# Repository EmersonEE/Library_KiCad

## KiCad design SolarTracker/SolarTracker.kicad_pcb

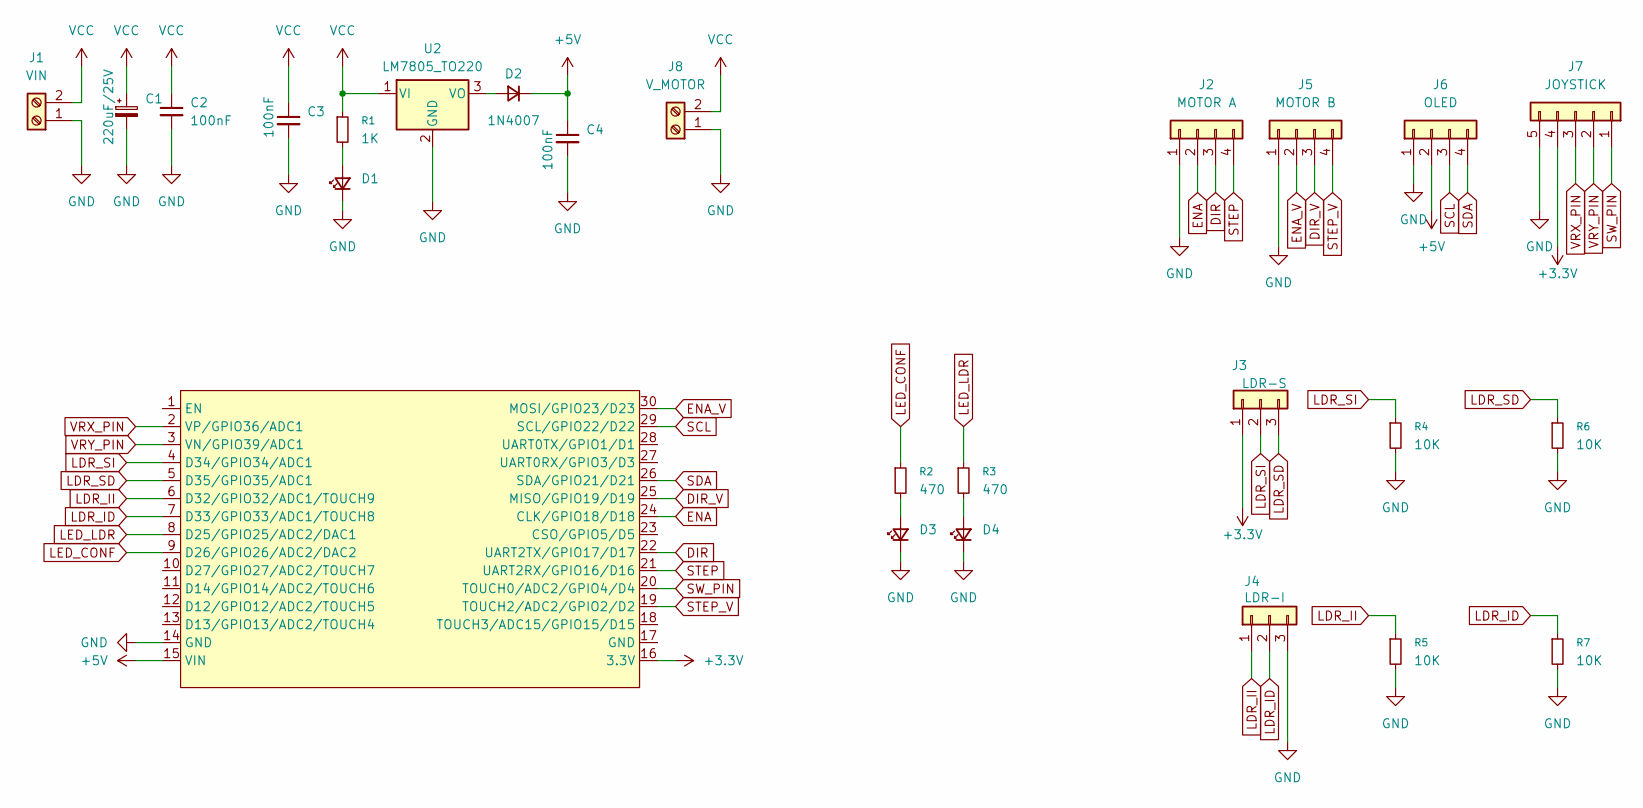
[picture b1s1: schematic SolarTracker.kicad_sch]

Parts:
C1: 220uF/25V; CP_Radial_D6.3mm_P2.50mm
C2, C3, C4: 100nF; C_Disc_D3.8mm_W2.6mm_P2.50mm
D1, D3, D4: LED_D5.0mm
D2: 1N4007; D_A-405_P10.16mm_Horizontal
J1: VIN; TerminalBlock_Phoenix_MKDS-1,5-2-5.08_1x02_P5.08mm_Horizont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
J2: MOTOR A; Molex_KK-254_AE-6410-04A_1x04_P2.54mm_Vertical
J3: LDR-S; Molex_KK-254_AE-6410-03A_1x03_P2.54mm_Vertical
J4: LDR-I; Molex_KK-254_AE-6410-03A_1x03_P2.54mm_Vertical
J5: MOTOR B; Molex_KK-254_AE-6410-04A_1x04_P2.54mm_Vertical
J6: OLED; PinSocket_1x04_P2.54mm_Vertical
J7: JOYSTICK; PinSocket_1x05_P2.54mm_Vertical
J8: V_MOTOR; TerminalBlock_Phoenix_MKDS-1,5-2-5.08_1x02_P5.08mm_Horizont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
R1: 1K; R_Axial_DIN0207_L6.3mm_D2.5mm_P10.16mm_Horizontal
R2, R3: 470; R_Axial_DIN0207_L6.3mm_D2.5mm_P10.16mm_Horizontal
R4, R5, R6, R7: 10K; R_Axial_DIN0207_L6.3mm_D2.5mm_P10.16mm_Horizontal
U1: ESP32_DevKit_V1_DOIT; ESP32_DEVKIT_V1_E32
U2: LM7805_TO220; TO-220-3_Vertical

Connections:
+3.3V: J3.1, J7.4, U1.16 (3.3V)
+5V: C4.1, D2.1 (K), J6.2, U1.15 (VIN)
DIR: J2.3, U1.22 (UART2TX/GPIO17/D17)
DIR_V: J5.3, U1.25 (MISO/GPIO19/D19)
ENA: J2.2, U1.24 (CLK/GPIO18/D18)
ENA_V: J5.2, U1.30 (MOSI/GPIO23/D23)
GND: C1.2, C2.2, C3.2, C4.2, D1.1 (K), D3.1 (K), D4.1 (K), J1.1, J2.1, J4.3, J5.1, J6.1, J7.5, J8.1, R4.2, R5.2, R6.2, R7.2, U1.14 (GND), U2.2 (GND)
LDR_ID: J4.2, R7.1, U1.7 (D33/GPIO33/ADC1/TOUCH8)
LDR_II: J4.1, R5.1, U1.6 (D32/GPIO32/ADC1/TOUCH9)
LDR_SD: J3.3, R6.1, U1.5 (D35/GPIO35/ADC1)
LDR_SI: J3.2, R4.1, U1.4 (D34/GPIO34/ADC1)
LED_CONF: R2.1, U1.9 (D26/GPIO26/ADC2/DAC2)
LED_LDR: R3.1, U1.8 (D25/GPIO25/ADC2/DAC1)
unnamed: D1.2 (A), R1.2
unnamed: D2.2 (A), U2.3 (VO)
unnamed: D3.2 (A), R2.2
unnamed: D4.2 (A), R3.2
SCL: J6.3, U1.29 (SCL/GPIO22/D22)
SDA: J6.4, U1.26 (SDA/GPIO21/D21)
STEP: J2.4, U1.21 (UART2RX/GPIO16/D16)
STEP_V: J5.4, U1.19 (TOUCH2/ADC2/GPIO2/D2)
SW_PIN: J7.1, U1.20 (TOUCH0/ADC2/GPIO4/D4)
VCC: C1.1, C2.1, C3.1, J1.2, J8.2, R1.1, U2.1 (VI)
VRX_PIN: J7.3, U1.2 (VP/GPIO36/ADC1)
VRY_PIN: J7.2, U1.3 (VN/GPIO39/ADC1)

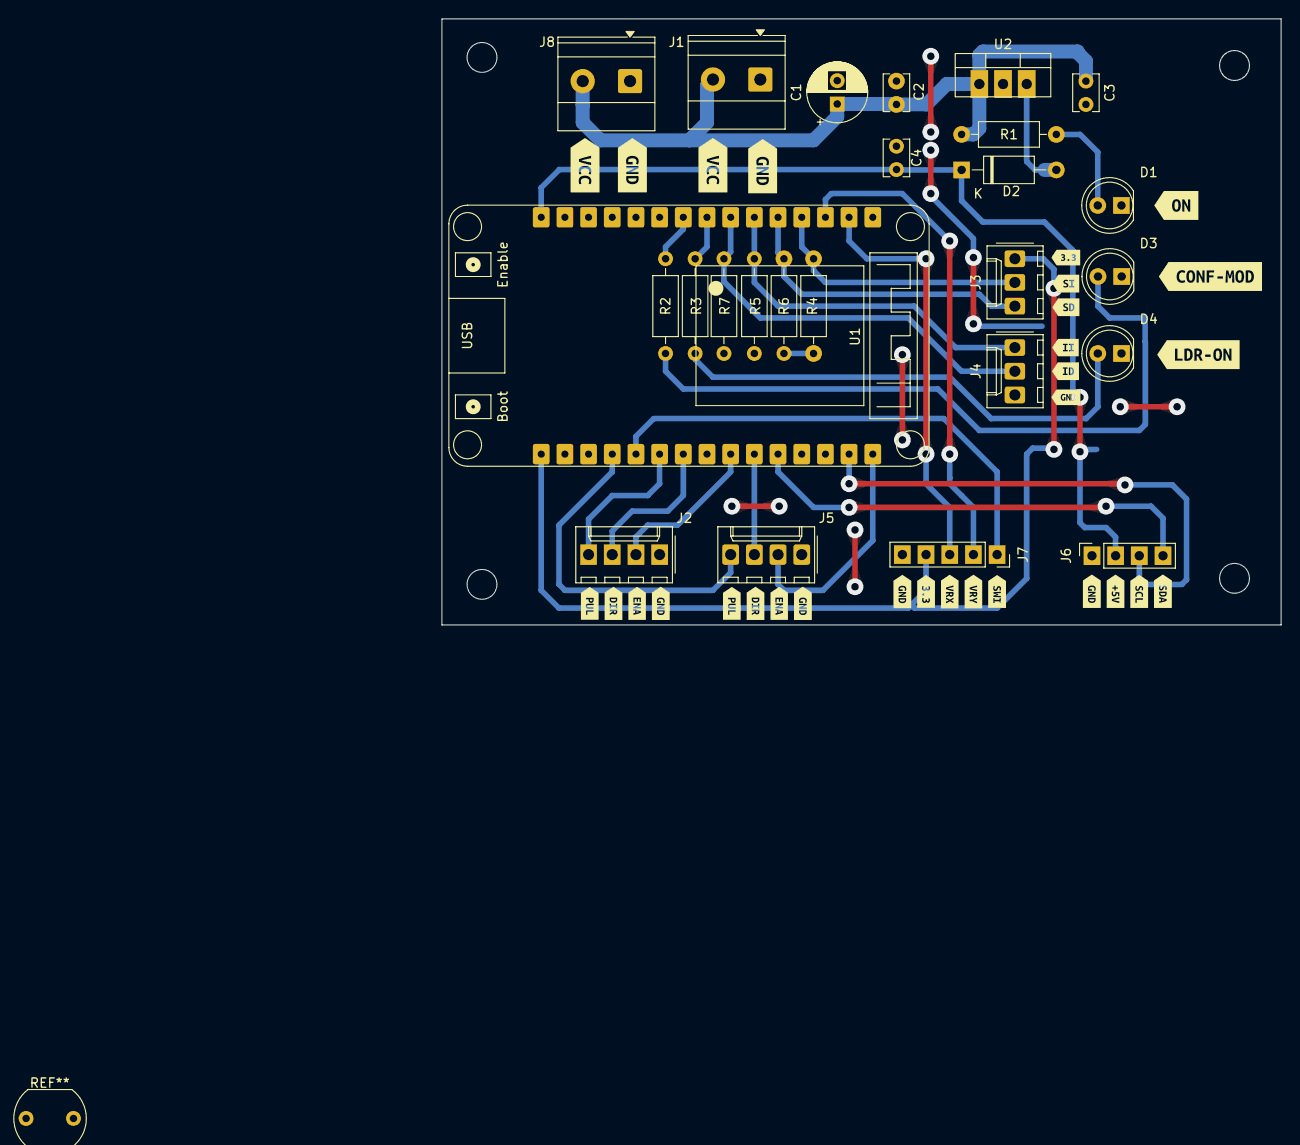
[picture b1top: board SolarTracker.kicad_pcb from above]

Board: 2 copper layers, 90.0 x 65.0 mm, 55 parts (0 on the bottom side), 25 nets.

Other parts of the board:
kibuzzard-67F1E4A8: G***; kibuzzard-67F1E4A8
kibuzzard-67F1E4B2: G***; kibuzzard-67F1E4B2
kibuzzard-67F1E4DB: G***; kibuzzard-67F1E4DB
kibuzzard-67F1E4E2: G***; kibuzzard-67F1E4E2
kibuzzard-67F1E4EA: G***; kibuzzard-67F1E4EA
kibuzzard-67F1E5DB, kibuzzard-67F1E5DB#2: G***; kibuzzard-67F1E5DB
kibuzzard-67F1E5E3, kibuzzard-67F1E5E3#2: G***; kibuzzard-67F1E5E3
kibuzzard-67F1E5F0, kibuzzard-67F1E5F0#2, kibuzzard-67F1E5F0#3: G***; kibuzzard-67F1E5F0
kibuzzard-67F1E6A7: G***; kibuzzard-67F1E6A7
kibuzzard-67F1E6AC: G***; kibuzzard-67F1E6AC
kibuzzard-67F1E47E: G***; kibuzzard-67F1E47E
kibuzzard-67F1E62A: G***; kibuzzard-67F1E62A
kibuzzard-67F1E66D: G***; kibuzzard-67F1E66D
kibuzzard-67F1E67F: G***; kibuzzard-67F1E67F
kibuzzard-67F1E69E: G***; kibuzzard-67F1E69E
kibuzzard-67F1E623: G***; kibuzzard-67F1E623
kibuzzard-67F1E673: G***; kibuzzard-67F1E673
kibuzzard-67F1E679: G***; kibuzzard-67F1E679
kibuzzard-67F1E689: G***; kibuzzard-67F1E689
kibuzzard-67F1ECE8: G***; kibuzzard-67F1ECE8
kibuzzard-67F1ECF6: G***; kibuzzard-67F1ECF6
kibuzzard-67F1ECFC: G***; kibuzzard-67F1ECFC
kibuzzard-67F1ED00: G***; kibuzzard-67F1ED00
kibuzzard-67F1ED0E: G***; kibuzzard-67F1ED0E
kibuzzard-67F1ED07: G***; kibuzzard-67F1ED07
kibuzzard-67F1ED13: G***; kibuzzard-67F1ED13

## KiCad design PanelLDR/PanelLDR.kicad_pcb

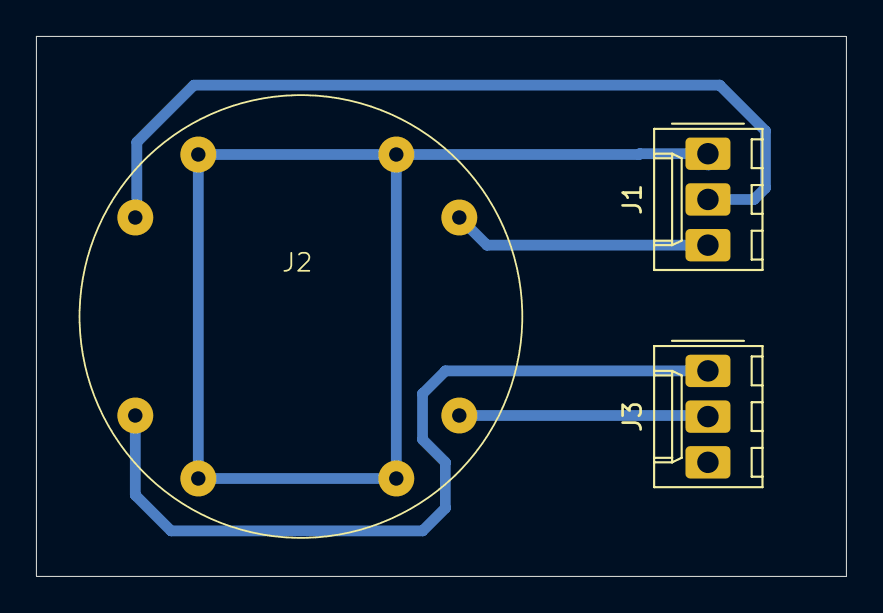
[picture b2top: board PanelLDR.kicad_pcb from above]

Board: 2 copper layers, 45.0 x 30.0 mm, 3 parts (0 on the bottom side), 5 nets.

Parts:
J1, J3: Conn_01x03; Molex_KK-254_AE-6410-03A_1x03_P2.54mm_Vertical
J2: Conn_01x08; LDR_PANEL

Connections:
+3.3V: J1.1, J2.2, J2.3, J2.6, J2.7
LDR_ID: J2.4, J3.2
LDR_II: J2.1, J3.1
LDR_SD: J1.3, J2.5
LDR_SI: J1.2, J2.8

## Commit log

2025-04-05 Subiendo El md
2025-04-05 Subiendo Las Librerias
2025-04-06 PCB Terminadas
2025-04-07 Placas Terminadas
